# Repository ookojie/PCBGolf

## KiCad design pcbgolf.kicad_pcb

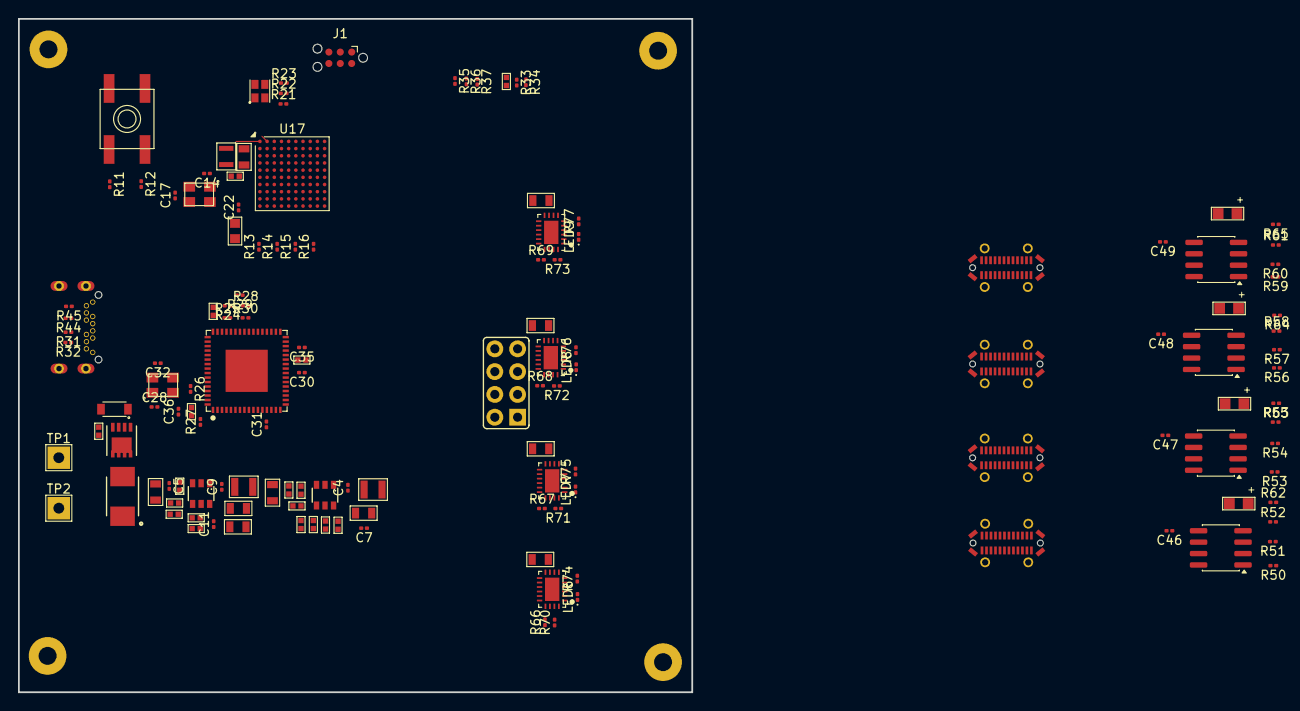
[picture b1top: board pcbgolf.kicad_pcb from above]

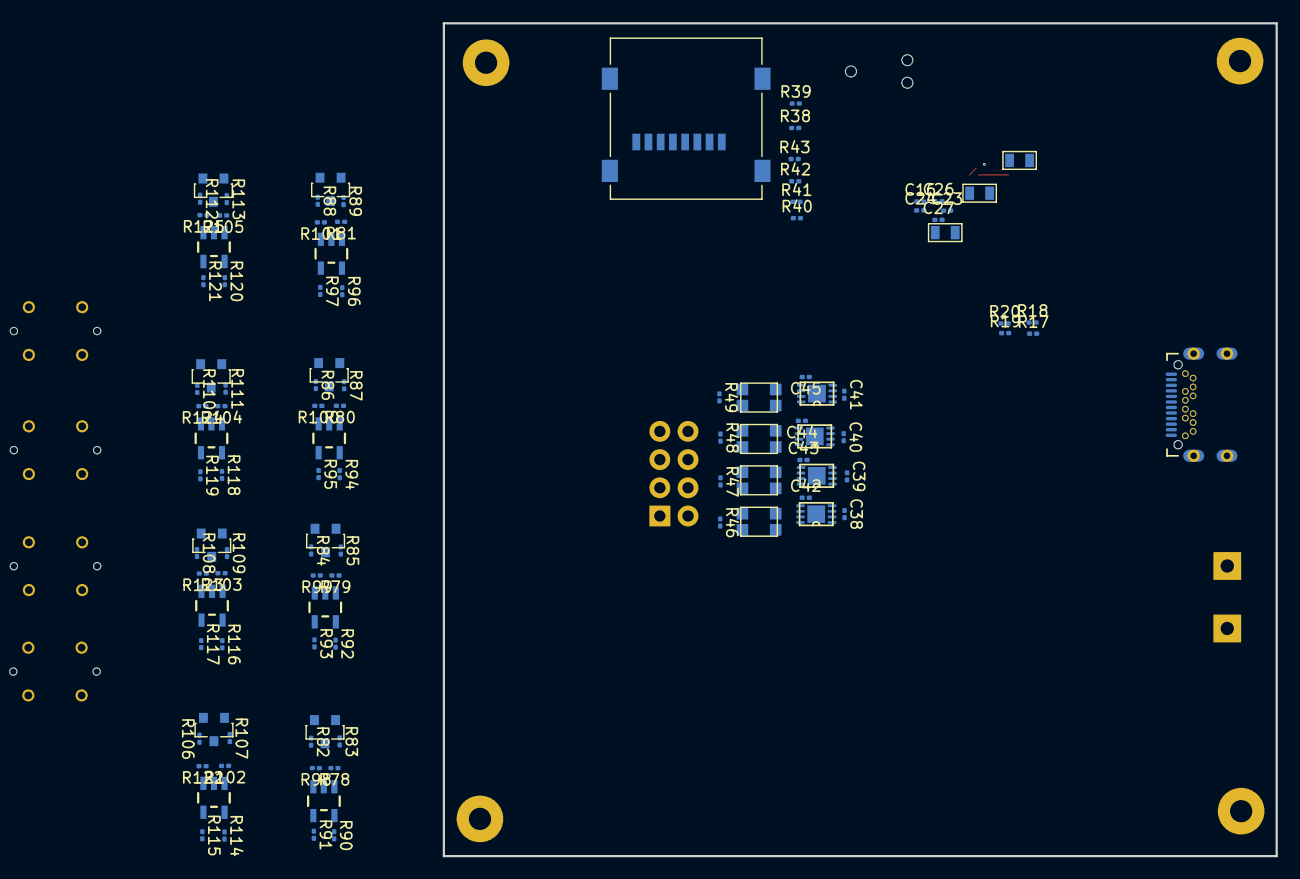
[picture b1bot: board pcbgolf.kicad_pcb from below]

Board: 2 copper layers, 75.0 x 75.0 mm, 246 parts (104 on the bottom side), 195 nets.

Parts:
BH1, BH2, BH3, BH4: M2_BOLT
C1, C3, C8, C12, C13, C15, C19, C20, C21: 10uF; 0805-C
C2: 100nF; 0402-C
C4, C5, C7, C9, C11, C16, C22, C23, C24, C26, C27, C30, C31, C35, C36, C38, C39, C40, C41, C42, C43, C44, C45, C46, C47, C48, C49: 100nF; C_0201_0603Metric
C6, C10: DNP; 0402-C
C14, C17, C28, C32: 12pF; C_0201_0603Metric
C25: 220pF; 0402-C
C29, C33, C34, C37: 10u; 0402-C
C50, C51, C52, C53: 10u; 0805-C
D1: TVS-BI-DO214AA; DO-214AA(SMB)
D2: DIODEDB2W40100L; SOD-123F
J1: Conn_ARM_SWD_TagConnect_TC2030-NL; Tag-Connect_TC2030-IDC-NL_2x03_P1.27mm_Vertical
J2: MICRO_SD-0472192001; 0472192001
J3: USB-C-FEMALE; DX07S024XJ1R1100
J4: CAN; 2X04
J5, J6, J7, J8: USB-C-FEMALEGCT; USB-C-FEMALE-VERT-GCT
L1, L2: 3u3; L-1008
L3: L-US-L2; 0603-L
L4: 2u2; 0806
L5, L6, L7, L8: ACT1210D_CHOKE; CHOKE-3.2X2.5
LED1: CREE-RGB-CLMVC
LED2: CAN0; CHIPLED
LED3: CAN1; CHIPLED
LED4: CAN2; CHIPLED
LED5: CAN3; CHIPLED
LED6, LED7, LED8, LED9: CH1_PWR; LED_0201_0603Metric
LED10, LED11, LED12, LED13, LED14, LED15, LED16, LED17: LED-CC-GREEN-RED-AM23ESG; SOT23-3
Q1: SIS427-VI; PP-1212-8
Q2, Q3, Q4, Q5, Q6, Q7, Q8, Q9: NFET-DUAL-COMMON-SOURCE-QS5K2; SOT23-5
R1, R3, R7, R8, R9: 10k; 0402-R
R2: 1k; 0402-R
R4, R5, R6: 100k; 0402-R
R10: 52k3; 0402-R
R11, R12, R28, R29, R30, R31, R32, R33, R34, R35, R36, R37, R44, R45, R50, R51, R53, R54, R56, R57, R59, R60, R78, R79, R80, R81, R98, R99, R100, R101, R102, R103, R104, R105, R122, R123, R124, R125: 10k; R_0201_0603Metric
R13, R14, R15, R16, R17, R18, R19, R20, R24, R25, R52, R55, R58, R61: 100k; R_0201_0603Metric
R21, R23, R90, R92, R94, R96, R114, R116, R118, R120: 1k; R_0201_0603Metric
R22, R62, R63, R64, R65: 2k7; R_0201_0603Metric
R26: 1M; R_0201_0603Metric
R27: 12k; R_0201_0603Metric
R38, R39, R40, R41, R42, R43: 0R; R_0201_0603Metric
R46, R47, R48, R49: 60; R_0201_0603Metric
R66, R67, R68, R69: 28k; R_0201_0603Metric
R70, R71, R72, R73: 33k; R_0201_0603Metric
R74, R75, R76, R77: 3k3; R_0201_0603Metric
R82, R83, R84, R85, R86, R87, R88, R89, R91, R93, R95, R97, R106, R107, R108, R109, R110, R111, R112, R113, R115, R117, R119, R121: 100; R_0201_0603Metric
SW1: SPST-2-4PIN; EVQ-Q2
TP1, TP2: TestPoint; TestPoint_THTPad_2.5x2.5mm_Drill1.2mm
U1, U2: AP62300T; SOT23-6
U4: USB2517; QFN64-9X9
U5, U6, U7, U8: MCP2542FDT-E/MNY; TDFN8_2X3MC_MCH
U9, U10, U11, U12: NCS20071XV; SOIC-8_3.9x4.9mm_P1.27mm
U13, U14, U15, U16: TPS25942; WQFN20
U17: STM32H725VGHx; TFBGA-100_8x8mm_Layout10x10_P0.8mm
Y1: 25MHz; XTAL-3.2X2.5
Y2: 24MHz; XTAL-3.2X2.5

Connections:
+3V3: C6.2, C7.1, C8.1, C19.1, C20.1, C23.1, C24.1, C26.1, C27.1, C30.2, C31.2, C37.1, C42.1, C43.1, C44.1, C45.1, J1.1 (VCC), J2.4 (VDD), L1.2, L3.1, LED1.U1 (COM+), R4.1, R5.1, R6.1, R11.1, R28.1, R29.1, R30.1, R33.1, R34.1, R35.1, R36.1, R37.1, SW1.B (S), SW1.B' (S1), U4.5 (VDDA33), U4.10 (VDDA33), U4.13 (CFG_SEL2), U4.24 (VDD33CR), U4.42 (CFG_SEL1), U4.43 (RESET_N), U4.46 (VDD33), U4.52 (VDDA33), U4.57 (VDDA33), U4.64 (VDD33PLL), U5.5 (VIO), U6.5 (VIO), U7.5 (VIO), U8.5 (VIO), U17.C2 (VBAT), U17.D6 (VDD), U17.E5 (VDD), U17.E8 (VDD33USB), U17.F6 (VDD)
+5V: C1.1, C2.1, C10.2, C11.1, C12.1, C13.1, C38.1, C39.1, C40.1, C41.1, L2.2, R1.1, R10.2, R52.2, R55.2, R58.2, R61.2, U1.3 (IN), U5.3 (VDD), U6.3 (VDD), U7.3 (VDD), U8.3 (VDD)
+12V: C3.1, C5.1, C46.1, C47.1, C48.1, C49.1, C50.1, C51.1, C52.1, C53.1, D2.1 (C), Q1.1 (S), Q1.2 (S), Q1.3 (S), R7.1, U2.3 (IN), U9.5 (V+), U10.5 (V+), U11.5 (V+), U12.5 (V+), U13.9 (VIN), U13.10 (VIN), U13.11 (VIN), U13.12 (VIN), U13.13 (VIN), U14.9 (VIN), U14.10 (VIN), U14.11 (VIN), U14.12 (VIN), U14.13 (VIN), U15.9 (VIN), U15.10 (VIN), U15.11 (VIN), U15.12 (VIN), U15.13 (VIN), U16.9 (VIN), U16.10 (VIN), U16.11 (VIN), U16.12 (VIN), U16.13 (VIN)
BTN: R12.2, SW1.A, SW1.A' (P1), U17.A5 (BOOT0), U17.B2 (PC15)
CAN0_EN: U5.8 (STBY), U17.B5 (PB7)
CAN0_H: J4.2, J5.A2 (TX1+), J6.A2 (TX1+), J7.A2 (TX1+), J8.A2 (TX1+), L5.4, R46.2, R50.1
CAN0_L: J4.1, J5.A3 (TX1-), J6.A3 (TX1-), J7.A3 (TX1-), J8.A3 (TX1-), L5.3, R46.1, R51.1
CAN0_RX: U5.4 (RXD), U17.A4 (PB8)
CAN0_TX: U5.1 (TXD), U17.E3 (PB9)
CAN1_EN: U6.8 (STBY), U17.A2 (PE5)
CAN1_H: J4.4, J5.A11 (RX2+), J6.A11 (RX2+), J7.A11 (RX2+), J8.A11 (RX2+), L6.4, R47.2, R53.1
CAN1_L: J4.3, J5.A10 (RX2-), J6.A10 (RX2-), J7.A10 (RX2-), J8.A10 (RX2-), L6.3, R47.1, R54.1
CAN1_RX: U6.4 (RXD), U17.A6 (PB5)
CAN1_TX: U6.1 (TXD), U17.D4 (PB6)
CAN2_EN: U7.8 (STBY), U17.K10 (PB15)
CAN2_H: J4.6, J5.B2 (TX2+), J6.B2 (TX2+), J7.B2 (TX2+), J8.B2 (TX2+), L7.4, R48.2, R56.1
CAN2_L: J4.5, J5.B3 (TX2-), J6.B3 (TX2-), J7.B3 (TX2-), J8.B3 (TX2-), L7.3, R48.1, R57.1
CAN2_RX: U7.4 (RXD), U17.H10 (PD13)
CAN2_TX: U7.1 (TXD), U17.H9 (PD12)
CAN3_EN: U8.8 (STBY), U17.K9 (PB14)
CAN3_H: J4.8, J5.B11 (RX1+), J6.B11 (RX1+), J7.B11 (RX1+), J8.B11 (RX1+), L8.4, R49.2, R59.1
CAN3_L: J4.7, J5.B10 (RX1-), J6.B10 (RX1-), J7.B10 (RX1-), J8.B10 (RX1-), L8.3, R49.1, R60.1
CAN3_RX: U8.4 (RXD), U17.K8 (PB12)
CAN3_TX: U8.1 (TXD), U17.J8 (PB13)
CH1_D_N: J5.A7 (D-A), J5.B7 (D-B), U4.1 (USBDN1_DM)
CH1_D_P: J5.A6 (D+A), J5.B6 (D+B), U4.2 (USBDN1_DP)
CH1_IMON: R70.2, U13.19 (IMON), U17.H4 (PC4)
CH1_PWR_EN: U13.14 (EN), U17.A1 (PE6)
CH1_SBU1: J5.A8 (SBU1), R19.2, R90.2, R91.2
CH1_SBU1_IGN: Q2.1 (G1), R78.1, R83.2, U17.C7 (PD0)
CH1_SBU1_RELAY: Q2.3 (G2), R82.2, R98.2, U17.B8 (PD1)
CH1_SBU2: J5.B8 (SBU2), R20.2, R114.2, R115.2
CH1_SBU2_IGN: Q6.1 (G1), R102.1, R107.2, U17.A8 (PD3)
CH1_SBU2_RELAY: Q6.3 (G2), R106.2, R122.2, U17.B7 (PD4)
CH2_D_N: J6.A7 (D-A), J6.B7 (D-B), U4.3 (USBDN2_DM)
CH2_D_P: J6.A6 (D+A), J6.B6 (D+B), U4.4 (USBDN2_DP)
CH2_IMON: R71.2, U14.19 (IMON), U17.K5 (PB1)
CH2_PWR_EN: U14.14 (EN), U17.E10 (PA10)
CH2_SBU1: J6.A8 (SBU1), R15.2, R92.2, R93.2
CH2_SBU1_IGN: Q3.1 (G1), R79.1, R85.2, U17.G9 (PC7)
CH2_SBU1_RELAY: Q3.3 (G2), R84.2, R99.2, U17.A7 (PD6)
CH2_SBU2: J6.B8 (SBU2), R13.2, R116.2, R117.2
CH2_SBU2_IGN: Q7.1 (G1), R103.1, R109.2, U17.J9 (PD8)
CH2_SBU2_RELAY: Q7.3 (G2), R108.2, R123.2, U17.J10 (PD10)
CH3_D_N: J7.A7 (D-A), J7.B7 (D-B), U4.6 (USBDN3_DM)
CH3_D_P: J7.A6 (D+A), J7.B6 (D+B), U4.7 (USBDN3_DP)
CH3_IMON: R72.2, U15.19 (IMON), U17.K3 (PA7)
CH3_PWR_EN: U15.14 (EN), U17.F10 (PA8)
CH3_SBU1: J7.A8 (SBU1), R17.2, R94.2, R95.2
CH3_SBU1_IGN: Q4.1 (G1), R80.1, R87.2, U17.J5 (PB2)
CH3_SBU1_RELAY: Q4.3 (G2), R86.2, R100.2, U17.H7 (PD11)
CH3_SBU2: J7.B8 (SBU2), R18.2, R118.2, R119.2
CH3_SBU2_IGN: Q8.1 (G1), R104.1, R111.2, U17.H8 (PD9)
CH3_SBU2_RELAY: Q8.3 (G2), R110.2, R124.2, U17.J6 (PE8)
CH4_D_N: J8.A7 (D-A), J8.B7 (D-B), U4.8 (USBDN4_DM)
CH4_D_P: J8.A6 (D+A), J8.B6 (D+B), U4.9 (USBDN4_DP)
CH4_IMON: R73.2, U16.19 (IMON), U17.J3 (PA6)
CH4_PWR_EN: U16.14 (EN), U17.E9 (PA9)
CH4_SBU1: J8.A8 (SBU1), R16.2, R96.2, R97.2
CH4_SBU1_IGN: Q5.1 (G1), R81.1, R89.2, U17.K6 (PE9)
CH4_SBU1_RELAY: Q5.3 (G2), R88.2, R101.2, U17.G8 (PD15)
CH4_SBU2: J8.B8 (SBU2), R14.2, R120.2, R121.2
CH4_SBU2_IGN: Q9.1 (G1), R105.1, R113.2, U17.B4 (PE0)
CH4_SBU2_RELAY: Q9.3 (G2), R112.2, R125.2, U17.C4 (PE1)
GND: BH1.0 (1_0), BH2.0 (1_0), BH3.0 (1_0), BH4.0 (1_0), C1.2, C2.2, C3.2, C5.2, C7.2, C8.2, C11.2, C12.2, C13.2, C14.2, C15.2, C16.2, C17.2, C19.2, C20.2, C21.2, C22.2, C23.2, C24.2, C25.2, C26.2, C27.2, C28.2, C29.2, C30.1, C31.1, C32.2, C33.2, C34.2, C35.1, C36.1, C37.2, C38.2, C39.2, C40.2, C41.2, C42.2, C43.2, C44.2, C45.2, C46.2, C47.2, C48.2, C49.2, C50.2, C51.2, C52.2, C53.2, D1.1, J1.5 (GND), J2.6 (VSS), J2.G1 (GND), J2.G2 (GND), J2.G3 (GND), J2.G4 (GND), J3.A1 (GND), J3.A12 (GND), J3.B1 (GND), J3.B1T (GND), J3.B12 (GND), J3.B12T (GND), J3.S1B (SHIELDA), J3.S1T (SHIELDA), J3.S1TH (SHIELDA), J3.S2B (SHIELDA), J3.S2T (SHIELDA), J3.S2TH (SHIELDA), J3.S3B (SHIELDB), J3.S3T (SHIELDB), J3.S3TH (SHIELDB), J3.S4B (SHIELDB), J3.S4T (SHIELDB), J3.S4TH (SHIELDB), J5.A1 (GND), J5.A12 (GND), J5.B1 (GND), J5.B12 (GND), J5.S1 (SHIELDA), J5.S2 (SHIELDA), J5.S3 (SHIELDA), J5.S4 (SHIELDA), J5.S11 (SHIELDB), J5.S12 (SHIELDB), J5.S13 (SHIELDB), J5.S14 (SHIELDB), J6.A1 (GND), J6.A12 (GND), J6.B1 (GND), J6.B12 (GND), J6.S1 (SHIELDA), J6.S2 (SHIELDA), J6.S3 (SHIELDA), J6.S4 (SHIELDA), J6.S11 (SHIELDB), J6.S12 (SHIELDB), J6.S13 (SHIELDB), J6.S14 (SHIELDB), J7.A1 (GND), J7.A12 (GND), J7.B1 (GND), J7.B12 (GND), J7.S1 (SHIELDA), J7.S2 (SHIELDA), J7.S3 (SHIELDA), J7.S4 (SHIELDA), J7.S11 (SHIELDB), J7.S12 (SHIELDB), J7.S13 (SHIELDB), J7.S14 (SHIELDB), J8.A1 (GND), J8.A12 (GND), J8.B1 (GND), J8.B12 (GND), J8.S1 (SHIELDA), J8.S2 (SHIELDA), J8.S3 (SHIELDA), J8.S4 (SHIELDA), J8.S11 (SHIELDB), J8.S12 (SHIELDB), J8.S13 (SHIELDB), J8.S14 (SHIELDB), LED2.C, LED3.C, LED4.C, LED5.C, LED6.1 (K), LED7.1 (K), LED8.1 (K), LED9.1 (K), LED10.3 (C), LED11.3 (C), LED12.3 (C), LED13.3 (C), LED14.3 (C), LED15.3 (C), LED16.3 (C), LED17.3 (C), Q2.2 (S), Q3.2 (S), Q4.2 (S), Q5.2 (S), Q6.2 (S), Q7.2 (S), Q8.2 (S), Q9.2 (S), R2.1, R3.2, R8.2, R9.2, R12.1, R25.1, R27.1, R31.2, R32.2, R44.2, R45.2, R66.1, R67.1, R68.1, R69.1, R70.1, R71.1, R72.1, R73.1, R78.2, R79.2, R80.2, R81.2, R98.1, R99.1, R100.1, R101.1, R102.2, R103.2, R104.2, R105.2, R122.1, R123.1, R124.1, R125.1, TP2.1 (1_1), U1.1 (GND), U2.1 (GND), U4.19 (TEST), U4.PAD (VSS), U5.2 (VSS), U5.PAD (EPAD), U6.2 (VSS), U6.PAD (EPAD), U7.2 (VSS), U7.PAD (EPAD), U8.2 (VSS), U8.PAD (EPAD), U9.2 (V-), U10.2 (V-), U11.2 (V-), U12.2 (V-), U13.3 (PGTH), U13.15 (OVP), U13.16 (GND), U13.PAD (GND), U14.3 (PGTH), U14.15 (OVP), U14.16 (GND), U14.PAD (GND), U15.3 (PGTH), U15.15 (OVP), U15.16 (GND), U15.PAD (GND), U16.3 (PGTH), U16.15 (OVP), U16.16 (GND), U16.PAD (GND), U17.C1 (VSS), U17.D1 (VSSSMPS), U17.D5 (VSS), U17.E7 (VSS), U17.F5 (VSS), U17.H2 (VSSA), Y1.2 (3), Y1.4 (3), Y2.2 (3), Y2.4 (3)
HUB_SCL: R30.2, U4.41 (SCL), U17.K7 (PB10)
HUB_SDA: R28.2, U4.40 (SDA), U17.J7 (PB11)
LED_B: R23.2, U17.A3 (PE2)
LED_G: R22.2, U17.B3 (PE3)
LED_R: R21.2, U17.C3 (PE4)
unnamed: D1.2, Q1.5 (D), Q1.6 (D), Q1.7 (D), Q1.8 (D), Q1.9 (D), TP1.1 (1_1)
unnamed: D2.2 (A), Q1.4 (G), R2.2
unnamed: J2.2 (CD/DAT3), R36.2, R41.2
unnamed: J2.5 (CLK), R43.2
unnamed: J2.3 (CMD), R37.2, R42.2
unnamed: J2.7 (DAT0), R33.2, R38.2
unnamed: J2.8 (DAT1), R34.2, R39.2
unnamed: J2.1 (DAT2), R35.2, R40.2
unnamed: J3.A5 (CC1), R31.1, R32.1
unnamed: J3.B5 (CC2), J3.B5T (CC2), R44.1, R45.1
unnamed: J5.A4 (VBUS), J5.A9 (VBUS), J5.B4 (VBUS), J5.B9 (VBUS), R74.1, U13.4 (VOUT), U13.5 (VOUT), U13.6 (VOUT), U13.7 (VOUT), U13.8 (VOUT)
unnamed: J6.A4 (VBUS), J6.A9 (VBUS), J6.B4 (VBUS), J6.B9 (VBUS), R75.1, U14.4 (VOUT), U14.5 (VOUT), U14.6 (VOUT), U14.7 (VOUT), U14.8 (VOUT)
unnamed: J7.A4 (VBUS), J7.A9 (VBUS), J7.B4 (VBUS), J7.B9 (VBUS), R76.1, U15.4 (VOUT), U15.5 (VOUT), U15.6 (VOUT), U15.7 (VOUT), U15.8 (VOUT)
unnamed: J8.A4 (VBUS), J8.A9 (VBUS), J8.B4 (VBUS), J8.B9 (VBUS), R77.1, U16.4 (VOUT), U16.5 (VOUT), U16.6 (VOUT), U16.7 (VOUT), U16.8 (VOUT)
unnamed: LED1.U4 (B-), R23.1
unnamed: LED1.U3 (G-), R22.1
unnamed: LED1.U2 (R-), R21.1
unnamed: LED2.A, R62.2
unnamed: LED3.A, R63.2
unnamed: LED4.A, R64.2
unnamed: LED5.A, R65.2
unnamed: LED6.2 (A), R74.2
unnamed: LED7.2 (A), R75.2
unnamed: LED8.2 (A), R76.2
unnamed: LED9.2 (A), R77.2
unnamed: LED10.2 (AG), R82.1
unnamed: LED10.1 (AR), R83.1
unnamed: LED11.2 (AG), R84.1
unnamed: LED11.1 (AR), R85.1
unnamed: LED12.2 (AG), R86.1
unnamed: LED12.1 (AR), R87.1
unnamed: LED13.2 (AG), R88.1
unnamed: LED13.1 (AR), R89.1
unnamed: LED14.2 (AG), R106.1
unnamed: LED14.1 (AR), R107.1
unnamed: LED15.2 (AG), R108.1
unnamed: LED15.1 (AR), R109.1
unnamed: LED16.2 (AG), R110.1
unnamed: LED16.1 (AR), R111.1
unnamed: LED17.2 (AG), R112.1
unnamed: LED17.1 (AR), R113.1
unnamed: Q2.5 (D1), R90.1
unnamed: Q2.4 (D2), R91.1
unnamed: Q3.5 (D1), R92.1
unnamed: Q3.4 (D2), R93.1
unnamed: Q4.5 (D1), R94.1
unnamed: Q4.4 (D2), R95.1
unnamed: Q5.5 (D1), R96.1
unnamed: Q5.4 (D2), R97.1
unnamed: Q6.5 (D1), R114.1
unnamed: Q6.4 (D2), R115.1
unnamed: Q7.5 (D1), R116.1
unnamed: Q7.4 (D2), R117.1
unnamed: Q8.5 (D1), R118.1
unnamed: Q8.4 (D2), R119.1
unnamed: Q9.5 (D1), R120.1
unnamed: Q9.4 (D2), R121.1
unnamed: R62.1, U9.4
unnamed: R63.1, U10.4
unnamed: R64.1, U11.4
unnamed: R65.1, U12.4
unnamed: C4.1, U1.6 (BST)
unnamed: R1.2, U1.5 (EN)
unnamed: C6.1, R3.1, R4.2, R5.2, R6.2, U1.4 (FB)
unnamed: C4.2, L1.1, U1.2 (SW)
unnamed: C9.1, U2.6 (BST)
unnamed: R7.2, R8.1, U2.5 (EN)
unnamed: C10.1, R9.1, R10.1, U2.4 (FB)
unnamed: C9.2, L2.1, U2.2 (SW)
unnamed: R27.2, U4.63 (RBIAS)
unnamed: R29.2, U4.45 (SUSP_IND)
unnamed: R24.1, R25.2, U4.44 (VBUS_DET)
unnamed: C33.1, C35.2, U4.25 (VDD18)
unnamed: C34.1, C36.2, U4.62 (VDD18PLL)
unnamed: C28.1, R26.2, U4.61 (XTAL1), Y2.1
unnamed: C32.1, R26.1, U4.60 (XTAL2), Y2.3 (2)
unnamed: L5.1, U5.7 (CANH)
unnamed: L5.2, U5.6 (CANL)
unnamed: L6.1, U6.7 (CANH)
unnamed: L6.2, U6.6 (CANL)
unnamed: L7.1, U7.7 (CANH)
unnamed: L7.2, U7.6 (CANL)
unnamed: L8.1, U8.7 (CANH)
unnamed: L8.2, U8.6 (CANL)
unnamed: R50.2, U9.1 (+)
unnamed: R51.2, R52.1, U9.3 (-)
unnamed: R53.2, U10.1 (+)
unnamed: R54.2, R55.1, U10.3 (-)
unnamed: R56.2, U11.1 (+)
unnamed: R57.2, R58.1, U11.3 (-)
unnamed: R59.2, U12.1 (+)
unnamed: R60.2, R61.1, U12.3 (-)
unnamed: R66.2, U13.17 (ILIM)
unnamed: R67.2, U14.17 (ILIM)
unnamed: R68.2, U15.17 (ILIM)
unnamed: R69.2, U16.17 (ILIM)
unnamed: R13.1, U17.J2 (PA1)
unnamed: R14.1, U17.H3 (PA2)
unnamed: R19.1, U17.K1 (PA4)
unnamed: R20.1, U17.K2 (PA5)
unnamed: R15.1, U17.K4 (PB0)
unnamed: R17.1, U17.F3 (PC0)
unnamed: R18.1, U17.F1 (PC1)
unnamed: R16.1, U17.J4 (PC5)
unnamed: R11.2, U17.D3 (PDR_ON)
unnamed: C14.1, U17.G1 (PH0), Y1.1
unnamed: C17.1, U17.G2 (PH1), Y1.3 (2)
SD_CLK: R43.1, U17.A10 (PC12)
SD_CMD: R42.1, U17.A9 (PD2)
SD_D0: R38.1, U17.G10 (PC8)
SD_D1: R39.1, U17.F9 (PC9)
SD_D2: R40.1, U17.B10 (PC10)
SD_D3: R41.1, U17.B9 (PC11)
STM_D_N: U4.55 (USBDN7_DM), U17.D10 (PA11)
STM_D_P: U4.56 (USBDN7_DP), U17.D9 (PA12)
SWD_NJTRST: J1.3 (~RESET), U17.C5 (PB4(NJTRST))
SWD_SWCLK: J1.4 (SWCLK), U17.C9 (PA14(JTCK)
SWD_SWDIO: J1.2 (SWDIO), U17.C10 (PA13(JTMS)
SWD_SWO: J1.6 (SWO), U17.B6 (PB3(JTDO)
USB_D_N: J3.A7 (D-A), J3.B7 (D-B), J3.B7T (D-B), U4.58 (USBUP_DM)
USB_D_P: J3.A6 (D+A), J3.B6 (D+B), J3.B6T (D+B), U4.59 (USBUP_DP)
VBUS: C29.1, J3.A4 (VBUS), J3.A9 (VBUS), J3.B4 (VBUS), J3.B4T (VBUS), J3.B9 (VBUS), J3.B9T (VBUS), R24.2
VDDA: C22.1, L3.2, U17.H1 (VDDA), U17.J1 (VREF+)
VDDLDO: C15.1, C16.1, C21.1, L4.1, U17.D8 (VCAP), U17.E1 (VDDSMPS), U17.E2 (VFBSMPS), U17.E6 (VDDLDO), U17.F7 (VDDLDO), U17.G6 (VCAP)
VLXSMPS: C25.1, L4.2, U17.D2 (VLXSMPS)
